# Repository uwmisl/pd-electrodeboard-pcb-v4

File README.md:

# Electrode Board v4

KiCad design for PurpleDrop electrode board with improved heater conductance, designed for 100x74mm film carrier and 50x50mm top plate.

This project is designed with KiCad v5.1.5.

## PDF Documentation

For a quick look, there is a [Schematic](PD_ElectrodeBoard_v4/outputs/PD_ElectrodeBoard_v4.1_sch.pdf) and [PCB fab drawing](PD_ElectrodeBoard_v4/outputs/PD_ElectrodeBoard_v4.1_fab.pdf)

## Project structure

Much of the board design is auto-generated by python scripts.

`FootprintGenerator.ipynb` generates the electrode and reservoir footprints.
They are all designed such that their origin should fall on the center of the
electrode "grid" positions. For this design, the pitch of the electrodes is
2.25mm. This script will generate a number of footprints, e.g. `electrode_points_1_40deg_rl.kicad_mod`.
The naming convention says that this footprint has 1 point per edge, the angle
of the points is 40 degrees, and it has points on the right and left edge (the
top and bottom are flat).

`FiducialFootprintGenerator.ipynb` generates a silkscreen footprint from an image file
(see `TagImages` directory), to put [april tags](https://github.com/AprilRobotics/apriltag)
onto the board as fidicuals for image processing. Each tag has a unique ID to aid in
identifying which tag (as well as which version of electrode board) has been
detected.

`LayoutGenerator.ipynb` generates a layout.yaml file for this
[kicad component layout plugin](https://github.com/mcbridejc/kicad_component_layout/).
This positions the electrodes, and selects between the different edge variants (e.g. trbl, tr)
based on neighboring electrodes in the grid.

This makes the process of experimenting with different electrode footprints and
layouts easier. Once the electrodes are positioned, the routing to the connectors
is done manually.

## BOM

| Part Number | Mfg | RefDes | Description | Qty |
| ----------- | --- | ------ | ----------- | --- |
| CLP-132-02-F-D-A  | Samtec | J1,J2  | 64-pin connectors      | 2   |
| 4929 | Keystone | H1-4 | #2-56 solderable threaded insert | 4 |
| PWR163S-25-25R0FE | Bourns | R1-4 | 25W resistor for heating | 4 |
| ZNI1000TA | Diodes Inc. | T1-4 | 1kohm RTD temperature sensor | 4 |
| S5B-PH-SM4-TB | JST | J3 | 5-pin connector for heaters | 1 |
| S8B-PH-SM4-TB | JST | J4 | 8-pin connector for RTDs | 1 |

## Revision History

### Version 4.1

- Shrinks width to fit reservoirs entirely under 50mmx50mm plate
- Corrects heater footprints
- Adds 2 internal layers to allow heaters to be located closer to the electrodes and
to provide additional thermal paths between them
- Flips connector pin labeling to match purpledrop
- 0.062" thick: 0.032" was not rigid enough
- Increases size of fiducials to 6mm and uses a unique value for each fiducial

### Version 4.0

Initial version

Issues:
- Undersized heating resistor footprints
- Mislabeled pin numbers (they do not match the purpledrop numbering)
- Fiducials were a bit too small; they silk screen resolution did not reproduce them well and sometimes they are difficult to detect

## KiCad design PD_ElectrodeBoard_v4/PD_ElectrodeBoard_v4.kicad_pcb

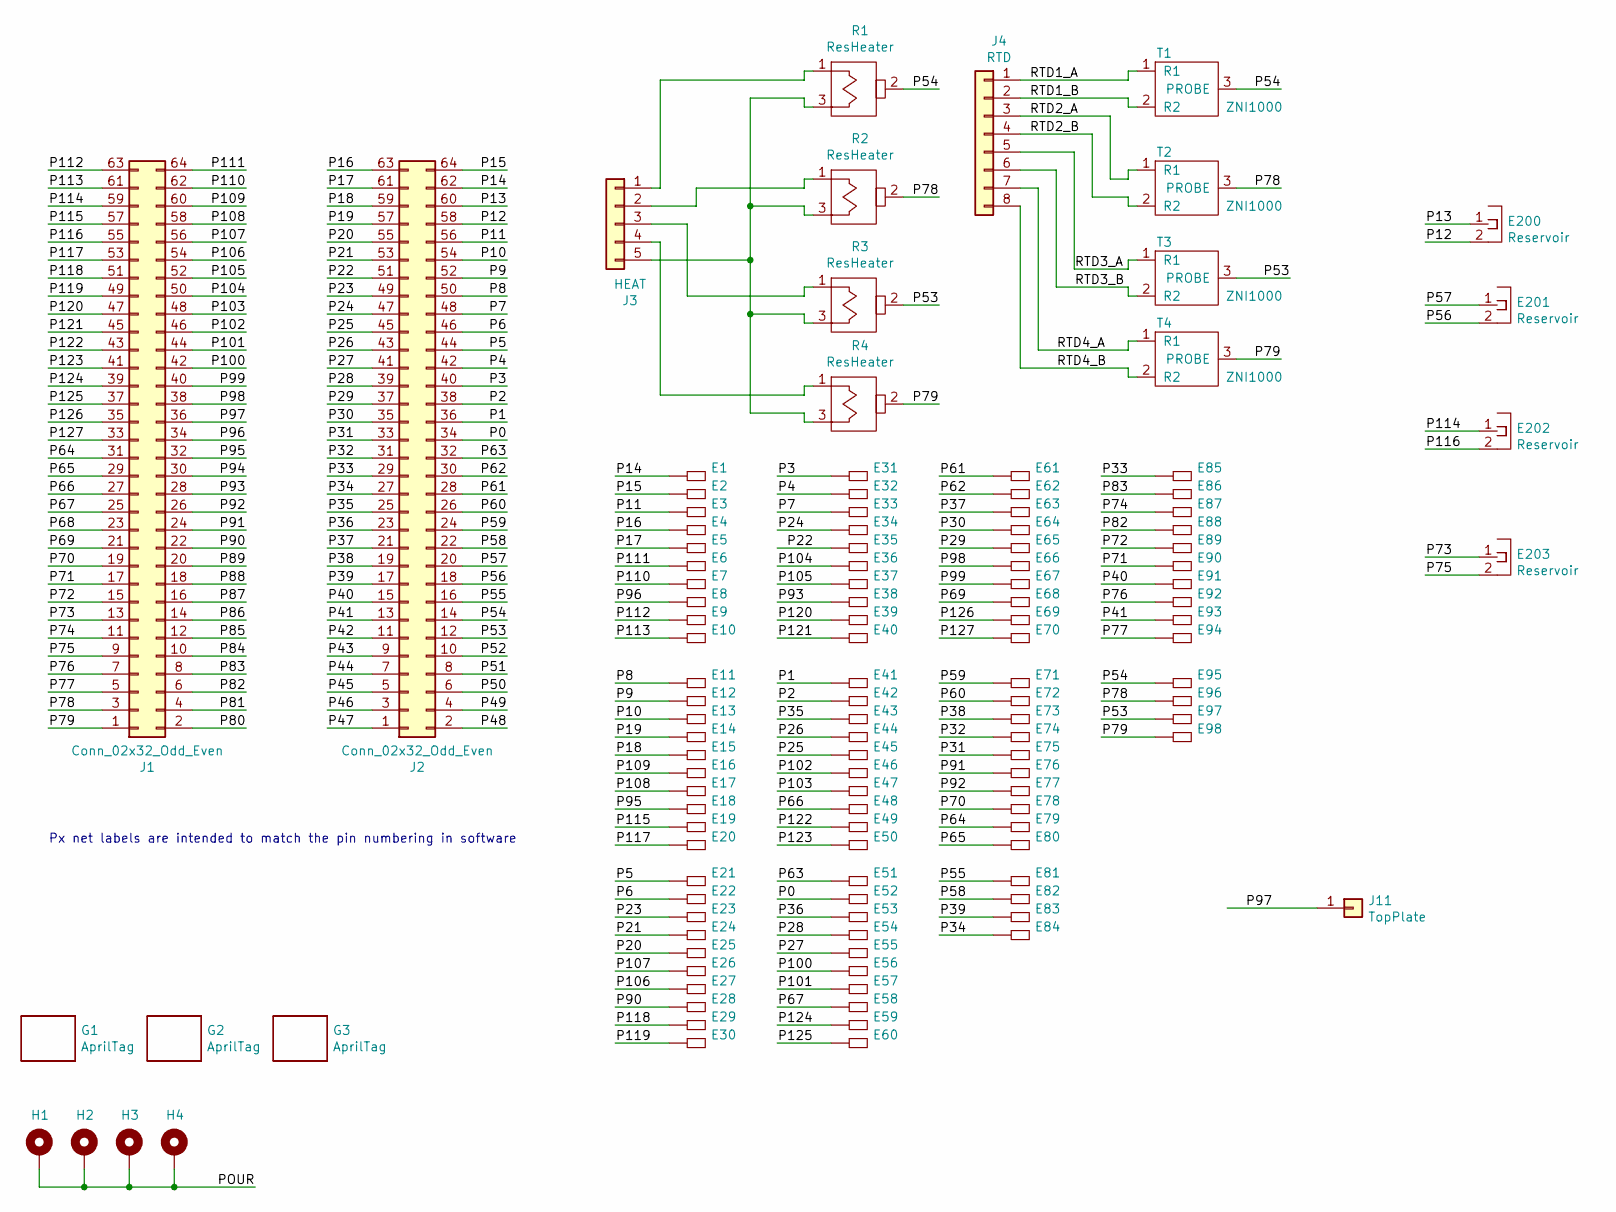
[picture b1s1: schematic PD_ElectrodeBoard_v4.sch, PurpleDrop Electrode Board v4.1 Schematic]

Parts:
E1, E2, E3, E4, E5, E6, E7, E8, E9, E10, E11, E12, E13, E14, E15, E16, E17, E18, E19, E20, E21, E22, E23, E24, E25, E26, E27, E28, E29, E30, E31, E32, E33, E34, E35, E36, E37, E38, E39, E40, E41, E42, E43, E44, E45, E46, E47, E48, E49, E50, E51, E52, E53, E54, E55, E56, E57, E58, E59, E60, E61, E62, E63, E64, E65, E66, E67, E68, E69, E70, E71, E72, E73, E74, E75, E76, E77, E78, E79, E80, E81, E82, E83, E84, E85, E86, E87, E88, E89, E90, E91, E92, E93, E94, E95, E96, E97, E98: DMFElectrode; electrode_points_1_40deg_trbl
E200, E201, E202, E203: Reservoir; reservoir_A_2.25mm
G1: AprilTag; tag36_11_00004_6.00mm
G2: AprilTag; tag36_11_00005_6.00mm
G3: AprilTag; tag36_11_00006_6.00mm
H1, H2, H3, H4: MountingHole_Pad; Keystone-4929
J1, J2: Conn_02x32_Odd_Even; CLP-132-02-F-D
J3: HEAT; JST_PH_S5B-PH-SM4-TB_1x05-1MP_P2.00mm_Horizontal
J4: RTD; JST_PH_S8B-PH-SM4-TB_1x08-1MP_P2.00mm_Horizontal
J11: TopPlate; TopPlatePad
R1, R2, R3, R4: ResHeater; PWR163_Resistor_DPAK
T1, T2, T3, T4: ZNI1000; SOT-23

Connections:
/P0: E52.1, J2.34
/P1: E41.1, J2.36
/P2: E42.1, J2.38
/P3: E31.1, J2.40
/P4: E32.1, J2.42
/P5: E21.1, J2.44
/P6: E22.1, J2.46
/P7: E33.1, J2.48
/P8: E11.1, J2.50
/P9: E12.1, J2.52
/P10: E13.1, J2.54
/P11: E3.1, J2.56
/P12: E200.2, J2.58
/P13: E200.1, J2.60
/P14: E1.1, J2.62
/P15: E2.1, J2.64
/P16: E4.1, J2.63
/P17: E5.1, J2.61
/P18: E15.1, J2.59
/P19: E14.1, J2.57
/P20: E25.1, J2.55
/P21: E24.1, J2.53
/P22: E35.1, J2.51
/P23: E23.1, J2.49
/P24: E34.1, J2.47
/P25: E45.1, J2.45
/P26: E44.1, J2.43
/P27: E55.1, J2.41
/P28: E54.1, J2.39
/P29: E65.1, J2.37
/P30: E64.1, J2.35
/P31: E75.1, J2.33
/P32: E74.1, J2.31
/P33: E85.1, J2.29
/P34: E84.1, J2.27
/P35: E43.1, J2.25
/P36: E53.1, J2.23
/P37: E63.1, J2.21
/P38: E73.1, J2.19
/P39: E83.1, J2.17
/P40: E91.1, J2.15
/P41: E93.1, J2.13
/P42: J2.11
/P43: J2.9
/P44: J2.7
/P45: J2.5
/P46: J2.3
/P47: J2.1
/P48: J2.2
/P49: J2.4
/P50: J2.6
/P51: J2.8
/P52: J2.10
/P53: E97.1, J2.12, R3.2 (TAB), T3.3 (PROBE)
/P54: E95.1, J2.14, R1.2 (TAB), T1.3 (PROBE)
/P55: E81.1, J2.16
/P56: E201.2, J2.18
/P57: E201.1, J2.20
/P58: E82.1, J2.22
/P59: E71.1, J2.24
/P60: E72.1, J2.26
/P61: E61.1, J2.28
/P62: E62.1, J2.30
/P63: E51.1, J2.32
/P64: E79.1, J1.31
/P65: E80.1, J1.29
/P66: E48.1, J1.27
/P67: E58.1, J1.25
/P68: J1.23
/P69: E68.1, J1.21
/P70: E78.1, J1.19
/P71: E90.1, J1.17
/P72: E89.1, J1.15
/P73: E203.1, J1.13
/P74: E87.1, J1.11
/P75: E203.2, J1.9
/P76: E92.1, J1.7
/P77: E94.1, J1.5
/P78: E96.1, J1.3, R2.2 (TAB), T2.3 (PROBE)
/P79: E98.1, J1.1, R4.2 (TAB), T4.3 (PROBE)
/P80: J1.2
/P81: J1.4
/P82: E88.1, J1.6
/P83: E86.1, J1.8
/P84: J1.10
/P85: J1.12
/P86: J1.14
/P87: J1.16
/P88: J1.18
/P89: J1.20
/P90: E28.1, J1.22
/P91: E76.1, J1.24
/P92: E77.1, J1.26
/P93: E38.1, J1.28
/P94: J1.30
/P95: E18.1, J1.32
/P96: E8.1, J1.34
/P97: J1.36, J11.1
/P98: E66.1, J1.38
/P99: E67.1, J1.40
/P100: E56.1, J1.42
/P101: E57.1, J1.44
/P102: E46.1, J1.46
/P103: E47.1, J1.48
/P104: E36.1, J1.50
/P105: E37.1, J1.52
/P106: E27.1, J1.54
/P107: E26.1, J1.56
/P108: E17.1, J1.58
/P109: E16.1, J1.60
/P110: E7.1, J1.62
/P111: E6.1, J1.64
/P112: E9.1, J1.63
/P113: E10.1, J1.61
/P114: E202.1, J1.59
/P115: E19.1, J1.57
/P116: E202.2, J1.55
/P117: E20.1, J1.53
/P118: E29.1, J1.51
/P119: E30.1, J1.49
/P120: E39.1, J1.47
/P121: E40.1, J1.45
/P122: E49.1, J1.43
/P123: E50.1, J1.41
/P124: E59.1, J1.39
/P125: E60.1, J1.37
/P126: E69.1, J1.35
/P127: E70.1, J1.33
/POUR: H1.1, H2.1, H3.1, H4.1
/RTD1_A: J4.1, T1.1 (R1)
/RTD1_B: J4.2, T1.2 (R2)
/RTD2_A: J4.3, T2.1 (R1)
/RTD2_B: J4.4, T2.2 (R2)
/RTD3_A: J4.5, T3.1 (R1)
/RTD3_B: J4.6, T3.2 (R2)
/RTD4_A: J4.7, T4.1 (R1)
/RTD4_B: J4.8, T4.2 (R2)
unnamed: J3.1, R1.1
unnamed: J3.2, R2.1
unnamed: J3.3, R3.1
unnamed: J3.4, R4.1
unnamed: J3.5, R1.3, R2.3, R3.3, R4.3

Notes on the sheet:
Px net labels are intended to match the pin numbering in software

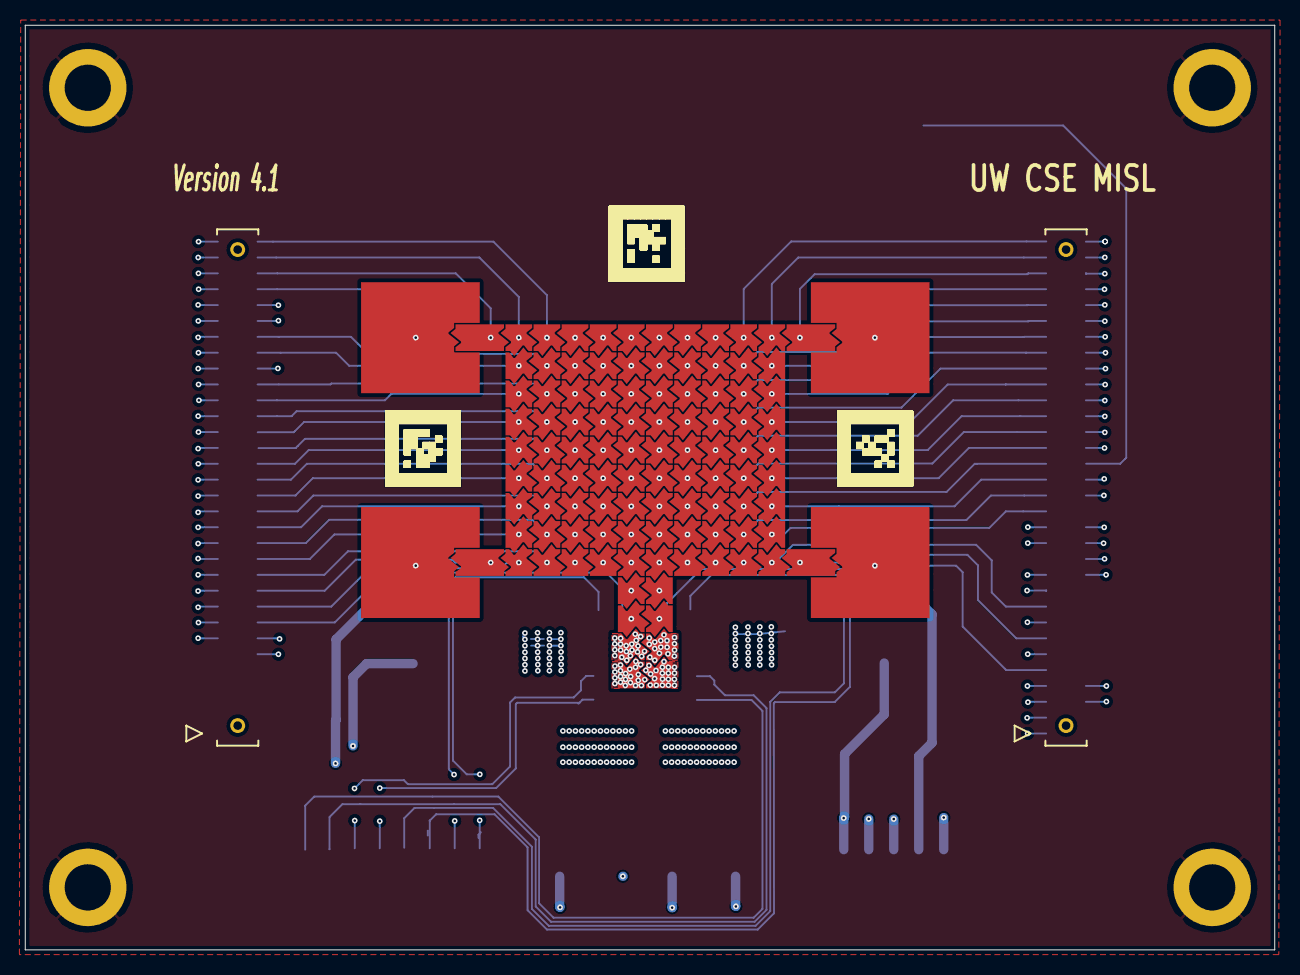
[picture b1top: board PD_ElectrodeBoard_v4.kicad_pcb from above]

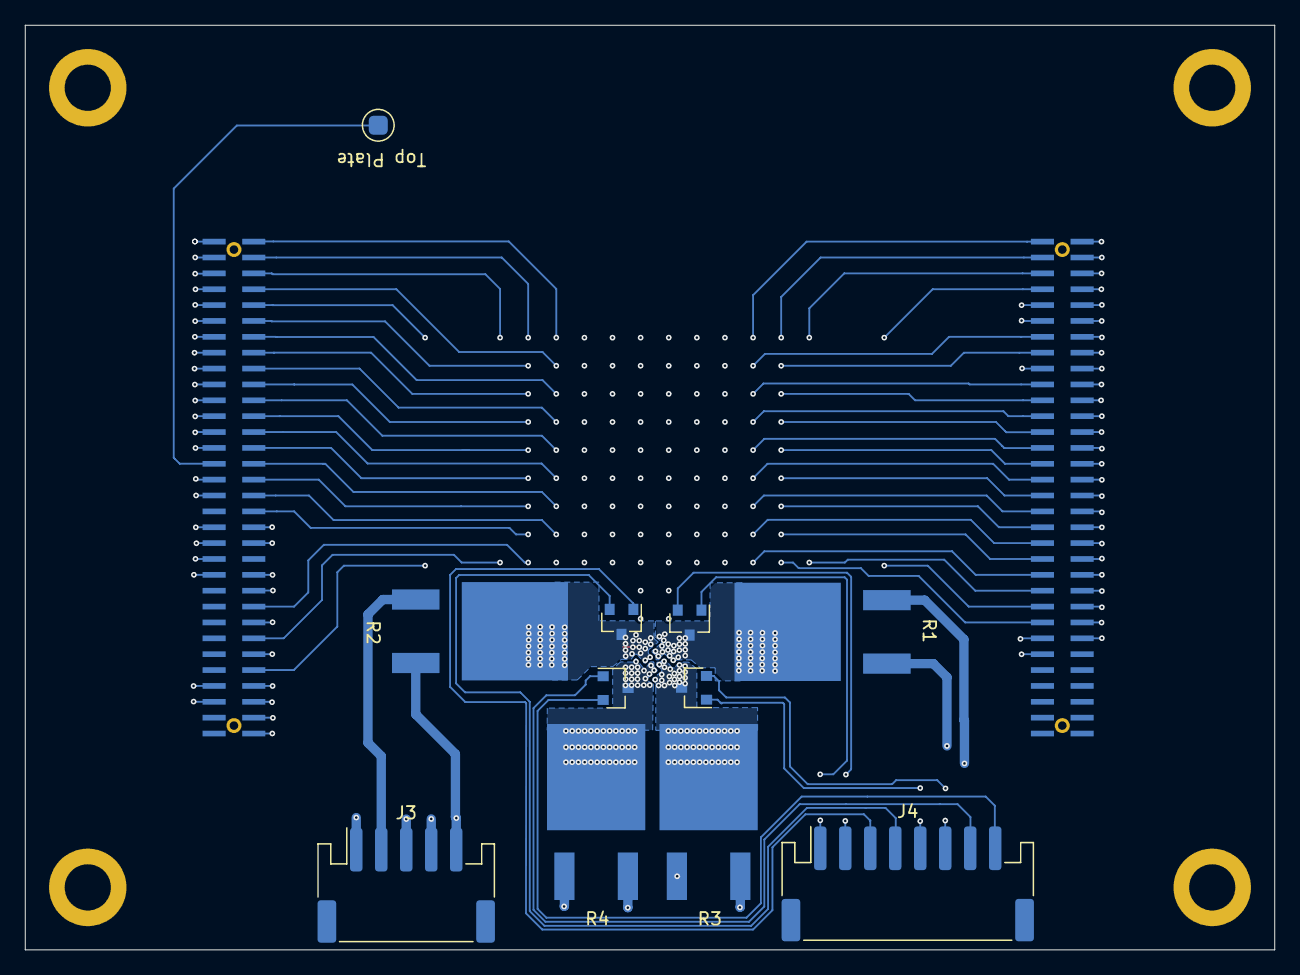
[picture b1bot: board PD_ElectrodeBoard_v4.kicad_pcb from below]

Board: 4 copper layers, 100.0 x 74.0 mm, 122 parts (11 on the bottom side), 121 nets.

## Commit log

2020-03-06 Add finished electrode board
2020-03-06 Add spacer project
2020-03-06 Add readme
2020-03-10 Add step file
2020-03-10 Re-export gerbers with drill files
2020-09-29 new revision 4.1 of electrode board
2021-04-05 Add JST footprint
2022-09-27 Add BOM info

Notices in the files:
parts and their libraries:
Copyright 2016 Accelerated Designs. All rights reserved.
